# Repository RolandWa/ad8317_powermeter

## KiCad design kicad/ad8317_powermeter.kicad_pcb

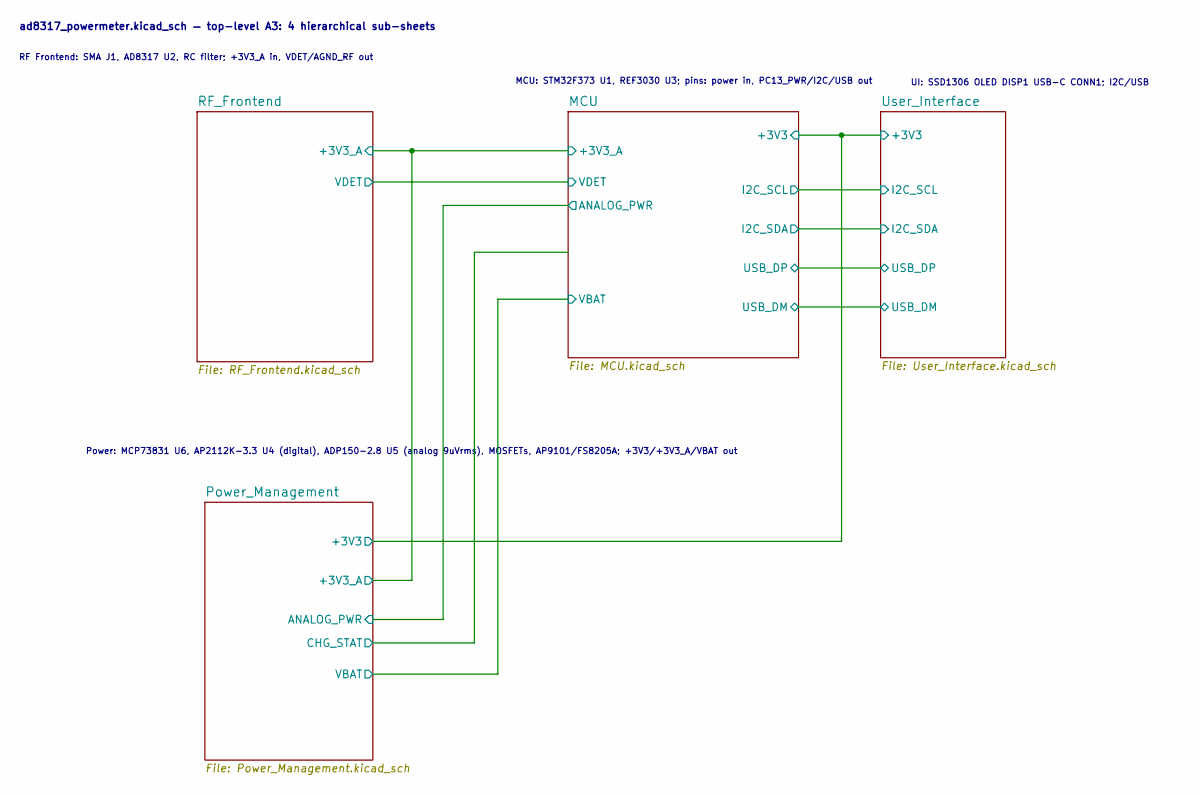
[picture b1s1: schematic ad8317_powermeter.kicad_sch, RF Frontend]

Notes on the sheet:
UI: SSD1306 OLED DISP1 USB-C CONN1; I2C/USB
MCU: STM32F373 U1, REF3030 U3; pins: power in, PC13_PWR/I2C/USB out
RF Frontend: SMA J1, AD8317 U2, RC filter; +3V3_A in, VDET/AGND_RF out
Power: MCP73831 U6, AP2112K-3.3 U4 (digital), ADP150-2.8 U5 (analog 9uVrms), MOSFETs, AP9101/FS8205A; +3V3/+3V3_A/VBAT out
ad8317_powermeter.kicad_sch — top-level A3: 4 hierarchical sub-sheets

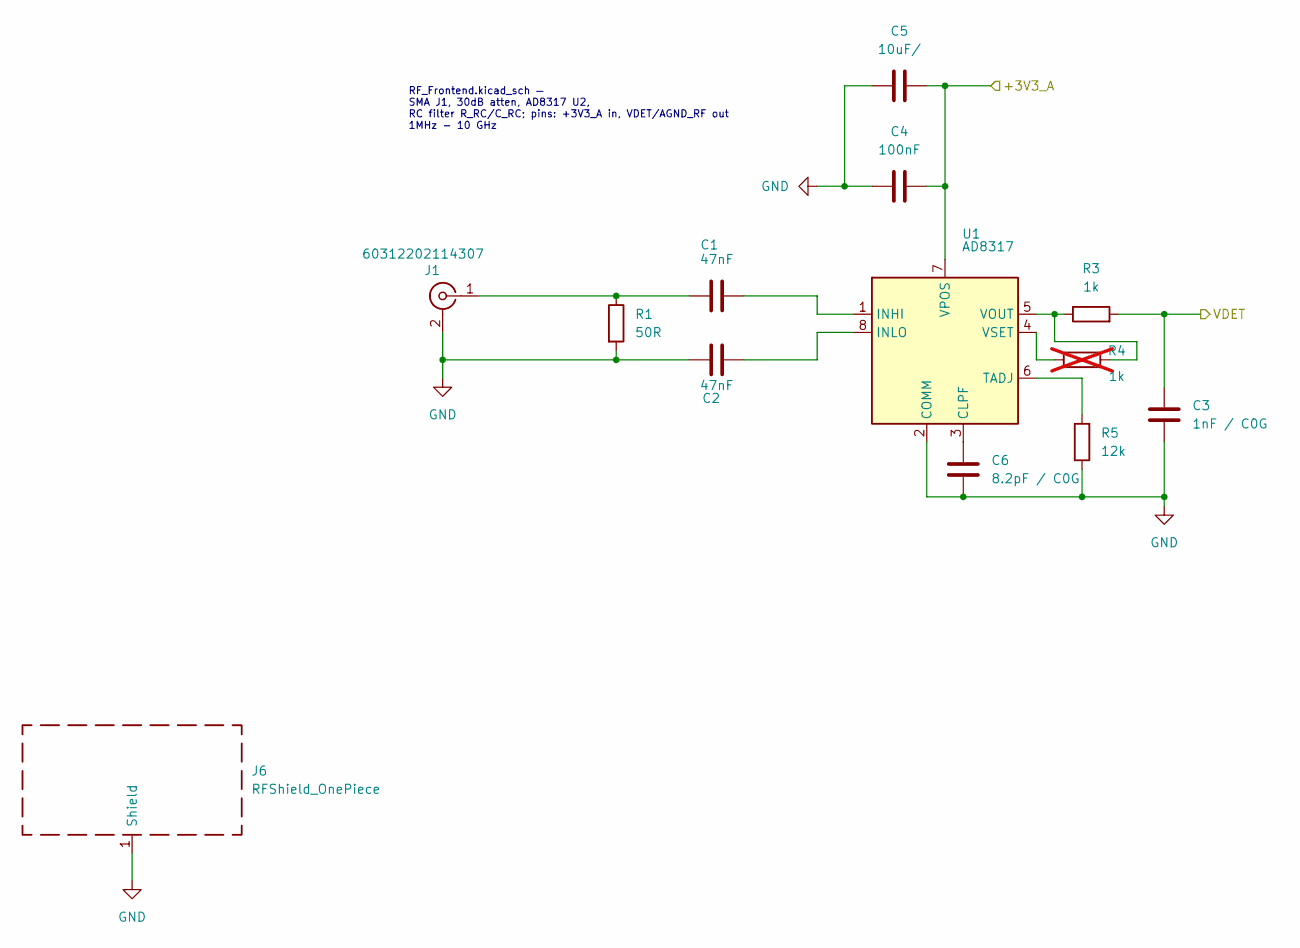
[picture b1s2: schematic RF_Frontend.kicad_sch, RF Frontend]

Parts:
C1, C2: 47nF; C_0402_1005Metric
C3: 1nF / C0G; C_0402_1005Metric
C4: 100nF; C_0402_1005Metric; LCSC C9900014224
C5: 10uF/; C_0805_2012Metric
C6: 8.2pF / C0G; C_0402_1005Metric
J1: 60312202114307; J_Wurth_WR-SMA_60312202114307; Part Number 60312202114307
J6: RFShield_OnePiece; Wuerth_36103305_30x30mm
R1: 50R; R_0402_1005Metric
R3: 1k; R_0402_1005Metric; LCSC C9900199398
R4: 1k; R_0402_1005Metric; not fitted
R5: 12k; R_0402_1005Metric
U1: AD8317; LFCSP-8-1EP_2x3mm_P0.5mm_EP1.6x2.34mm; MPN AD8317ACPZ-REEL7

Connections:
/MCU/+3V3_A: C4.2, C5.2, U1.7 (VPOS); also elsewhere on the board
/MCU/VDET: C3.2, R3.2; also elsewhere on the board
GND: C2.1, C3.1, C4.1, C5.1, C6.1, J1.2 (Ext), J6.1 (Shield_1), R1.2, R5.1, U1.2 (COMM), U1.9; also elsewhere on the board
unnamed: C1.1, J1.1 (In), R1.1
unnamed: C6.2, U1.3 (CLPF)
unnamed: C1.2, U1.1 (INHI)
unnamed: C2.2, U1.8 (INLO)
unnamed: R5.2, U1.6 (TADJ)
unnamed: R3.1, R4.2, U1.5 (VOUT)
unnamed: R4.1, U1.4 (VSET)

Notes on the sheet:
RF_Frontend.kicad_sch — SMA J1, 30dB atten, AD8317 U2, RC filter R_RC/C_RC; pins: +3V3_A in, VDET/AGND_RF out 1MHz - 10 GHz

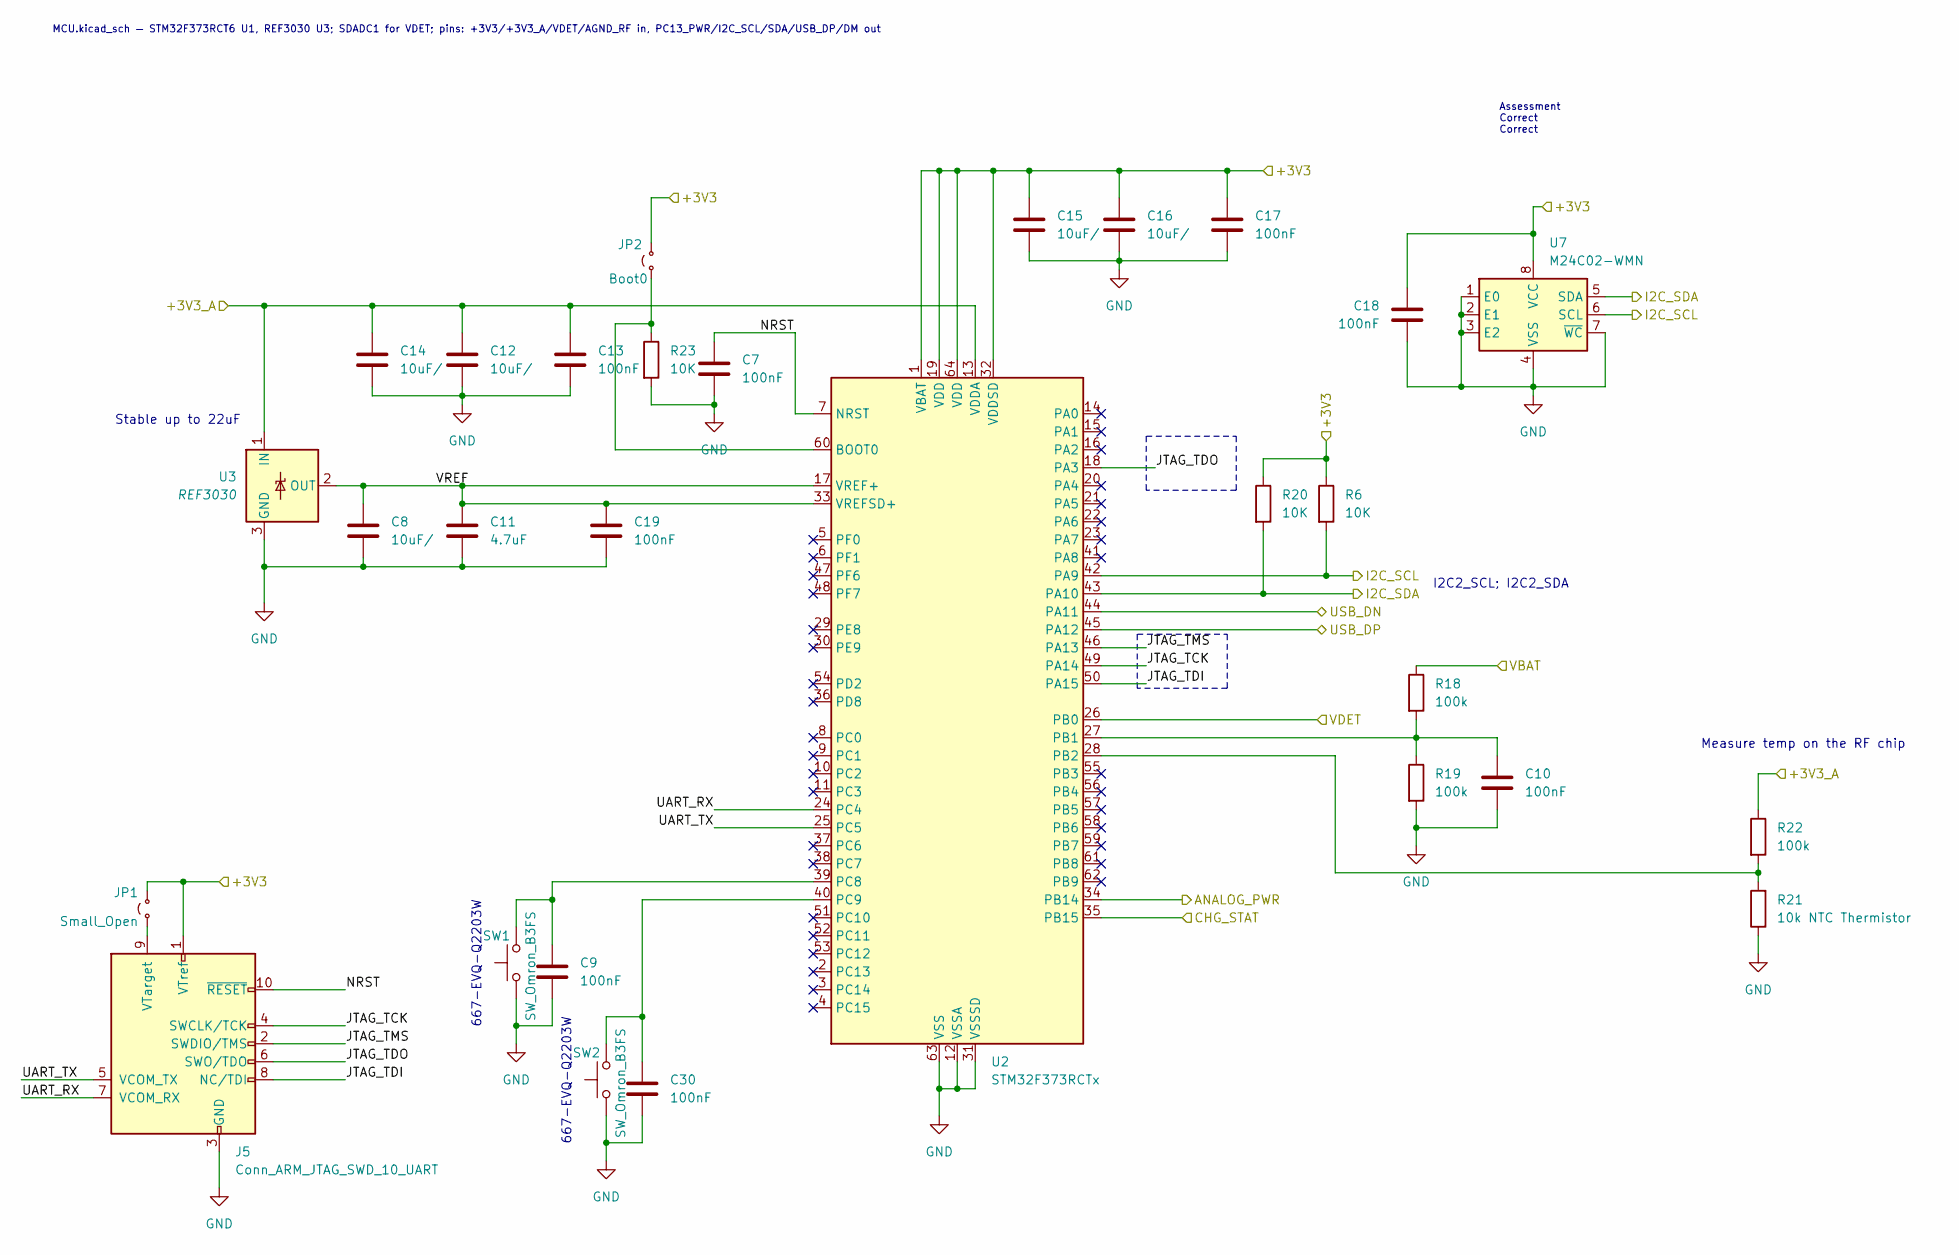
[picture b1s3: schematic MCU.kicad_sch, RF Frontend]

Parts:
C7, C9, C10, C13, C17, C18, C19, C30: 100nF; C_0402_1005Metric; LCSC C9900014224
C8, C12, C14, C15, C16: 10uF/; C_0805_2012Metric
C11: 4.7uF; C_0805_2012Metric
J5: Conn_ARM_JTAG_SWD_10_UART; PinHeader_2x05_P1.27mm_Vertical_SMD
JP1: Small_Open; SolderJumper-2_P1.3mm_Open_RoundedPad1.0x1.5mm
JP2: Boot0; SolderJumper-2_P1.3mm_Open_RoundedPad1.0x1.5mm
R6, R20, R23: 10K; R_0402_1005Metric
R18, R19, R22: 100k; R_0402_1005Metric
R21: 10k NTC Thermistor; C_0402_1005Metric; LCSC C2892547
SW1, SW2: SW_Omron_B3FS; SW_SPST_Omron_B3FS-100xP
U2: STM32F373RCTx; LQFP-64_10x10mm_P0.5mm
U3: REF3030; SOT-23
U7: M24C02-WMN; SOIC-8_3.9x4.9mm_P1.27mm

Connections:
/MCU/+3V3: C15.2, C16.2, C17.2, C18.1, J5.1 (VTref), JP1.2 (B), JP2.2 (B), R6.1, R20.1, U2.1 (VBAT), U2.19 (VDD), U2.32 (VDDSD), U2.64 (VDD), U7.8 (VCC); also elsewhere on the board
/MCU/+3V3_A: C12.2, C13.2, C14.2, R22.1, U2.13 (VDDA), U3.1 (IN); also elsewhere on the board
/MCU/ANALOG_PWR: U2.34 (PB14); also elsewhere on the board
/MCU/CHG_STAT: U2.35 (PB15); also elsewhere on the board
/MCU/I2C_SCL: R6.2, U2.42 (PA9), U7.6 (SCL); also elsewhere on the board
/MCU/I2C_SDA: R20.2, U2.43 (PA10), U7.5 (SDA); also elsewhere on the board
/MCU/JTAG_TCK: J5.4 (SWCLK/TCK), U2.49 (PA14)
/MCU/JTAG_TDI: J5.8 (NC/TDI), U2.50 (PA15)
/MCU/JTAG_TDO: J5.6 (SWO/TDO), U2.18 (PA3)
/MCU/JTAG_TMS: J5.2 (SWDIO/TMS), U2.46 (PA13)
/MCU/NRST: C7.2, J5.10 (~RESET), U2.7 (NRST)
/MCU/UART_RX: J5.7 (VCOM_RX), U2.24 (PC4)
/MCU/UART_TX: J5.5 (VCOM_TX), U2.25 (PC5)
/MCU/USB_DN: U2.44 (PA11); also elsewhere on the board
/MCU/USB_DP: U2.45 (PA12); also elsewhere on the board
/MCU/VBAT: R18.1; also elsewhere on the board
/MCU/VDET: U2.26 (PB0); also elsewhere on the board
/MCU/VREF: C8.2, C11.2, C19.2, U2.17 (VREF+), U2.33 (VREFSD+), U3.2 (OUT)
GND: C7.1, C8.1, C9.1, C10.1, C11.1, C12.1, C13.1, C14.1, C15.1, C16.1, C17.1, C18.2, C19.1, C30.1, J5.3 (GND), R19.2, R21.1, R23.2, SW1.1, SW2.1, U2.12 (VSSA), U2.31 (VSSSD), U2.63 (VSS), U3.3 (GND), U7.1 (E0), U7.2 (E1), U7.3 (E2), U7.4 (VSS), U7.7 (~WC); also elsewhere on the board
unnamed: J5.9 (VTarget), JP1.1 (A)
unnamed: JP2.1 (A), R23.1, U2.60 (BOOT0)
unnamed: C10.2, R18.2, R19.1, U2.27 (PB1)
unnamed: R21.2, R22.2, U2.28 (PB2)
unnamed: C9.2, SW1.2, U2.39 (PC8)
unnamed: C30.2, SW2.2, U2.40 (PC9)

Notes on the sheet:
Assessment Correct Correct
667-EVQ-Q2203W
Stable up to 22uF
Measure temp on the RF chip
MCU.kicad_sch — STM32F373RCT6 U1, REF3030 U3; SDADC1 for VDET; pins: +3V3/+3V3_A/VDET/AGND_RF in, PC13_PWR/I2C_SCL/SDA/USB_DP/DM out
I2C2_SCL; I2C2_SDA

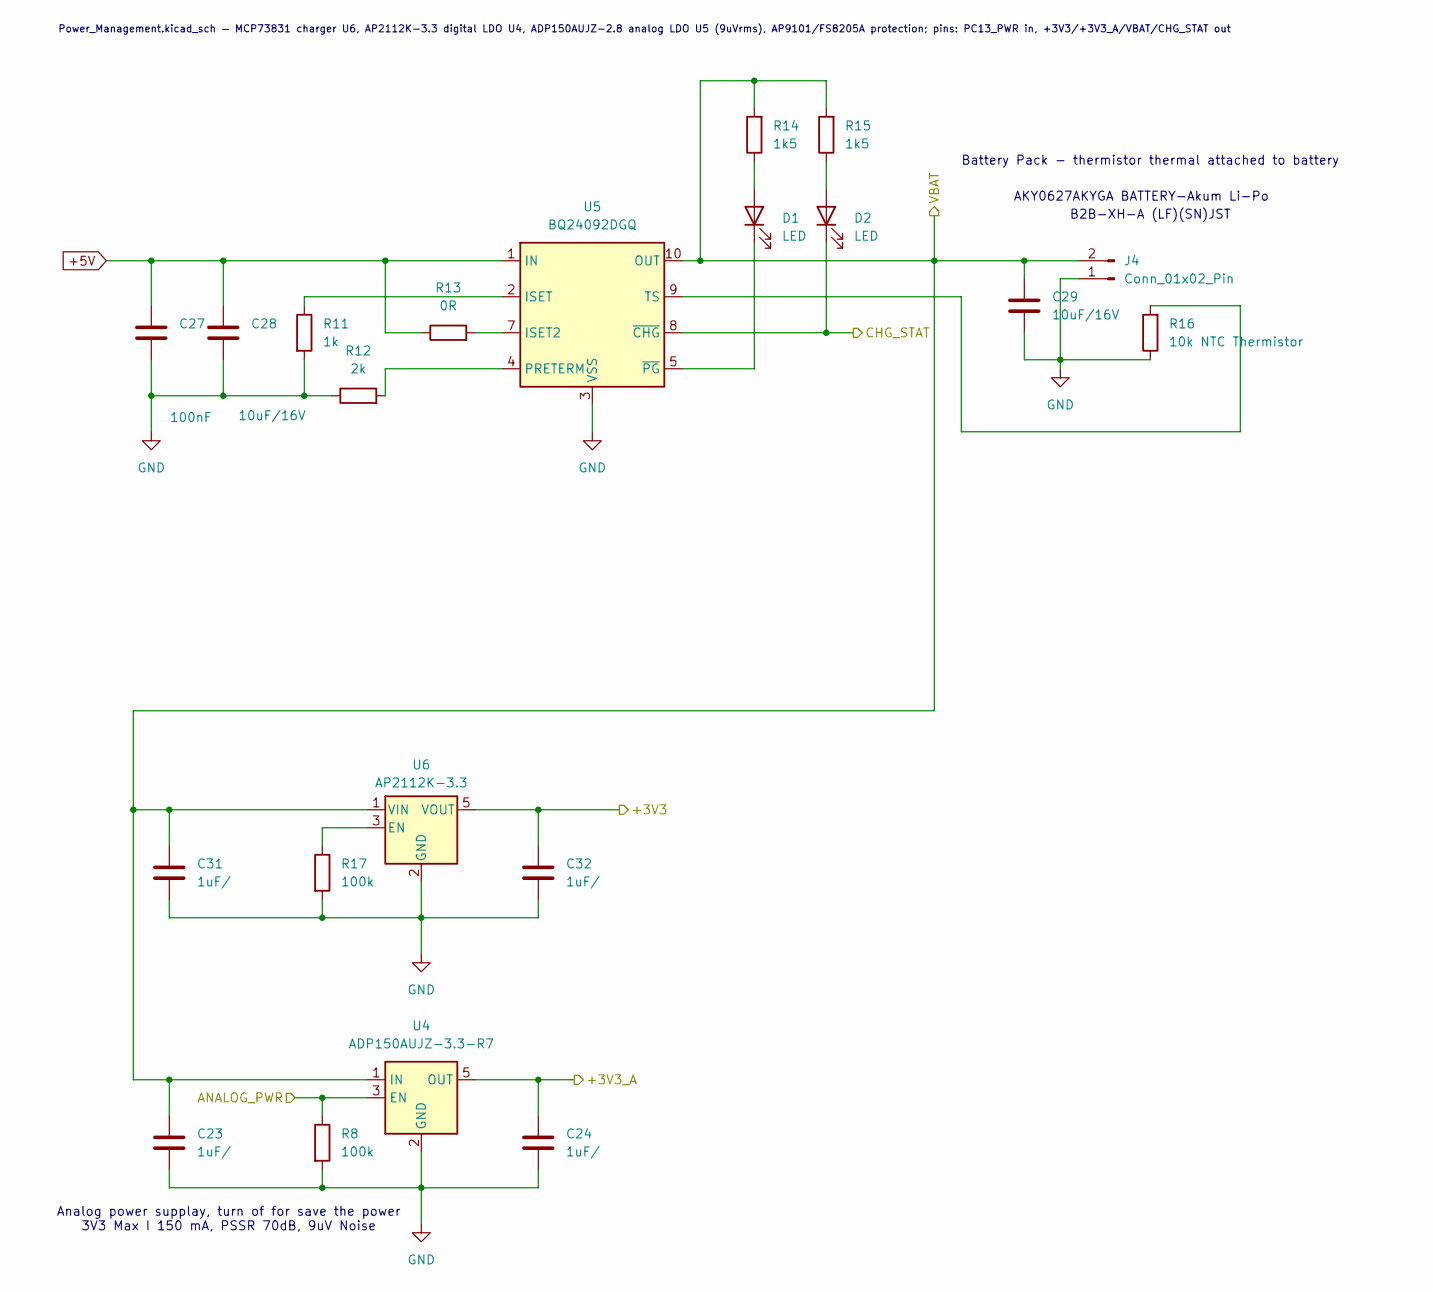
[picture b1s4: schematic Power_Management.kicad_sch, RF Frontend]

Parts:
C23, C24, C31, C32: 1uF/; C_0402_1005Metric
C27: 100nF; C_0402_1005Metric; LCSC C9900014224
C28, C29: 10uF/16V; C_0805_2012Metric; LCSC C9900019493
D1, D2: LED; LED_0402_1005Metric; LCSC C9900022508
J4: Conn_01x02_Pin; JST_XH_B2B-XH-AM_1x02_P2.50mm_Vertical; LCSC C161869
R8, R17: 100k; R_0402_1005Metric
R11: 1k; R_0402_1005Metric; LCSC C9900199398
R12: 2k; R_0402_1005Metric; LCSC C140225
R13: 0R; R_0402_1005Metric; LCSC C140225
R14, R15: 1k5; R_0402_1005Metric; LCSC C269672
R16: 10k NTC Thermistor; C_0402_1005Metric; LCSC C2892547
U4: ADP150AUJZ-3.3-R7; TSOT-23-5
U5: BQ24092DGQ; HVSSOP-10-1EP_3x3mm_P0.5mm_EP1.83x1.89mm_ThermalVias; Digikey BQ24092DGQT
U6: AP2112K-3.3; SOT-23-5

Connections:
+5V: C27.1, C28.1, R13.1, U5.1 (IN); also elsewhere on the board
/MCU/+3V3: C32.2, U6.5 (VOUT); also elsewhere on the board
/MCU/+3V3_A: C24.2, U4.5 (OUT); also elsewhere on the board
/MCU/ANALOG_PWR: R8.1, U4.3 (EN); also elsewhere on the board
/MCU/CHG_STAT: D2.1 (K), U5.8 (~CHG); also elsewhere on the board
/MCU/VBAT: C23.2, C29.1, C31.2, J4.2, R14.2, R15.2, U4.1 (IN), U5.10 (OUT), U6.1 (VIN); also elsewhere on the board
GND: C23.1, C24.1, C27.2, C28.2, C29.2, C31.1, C32.1, J4.1, R8.2, R11.2, R12.1, R16.1, R17.2, U4.2 (GND), U5.3 (VSS), U5.11 (VSS), U6.2 (GND); also elsewhere on the board
unnamed: D1.2 (A), R14.1
unnamed: D1.1 (K), U5.5 (~PG)
unnamed: D2.2 (A), R15.1
unnamed: R13.2, U5.7 (ISET2)
unnamed: R11.1, U5.2 (ISET)
unnamed: R12.2, U5.4 (PRETERM)
unnamed: R16.2, U5.9 (TS)
unnamed: R17.1, U6.3 (EN)

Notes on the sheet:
Battery Pack - thermistor thermal attached to battery
B2B-XH-A (LF)(SN)JST
Power_Management.kicad_sch — MCP73831 charger U6, AP2112K-3.3 digital LDO U4, ADP150AUJZ-2.8 analog LDO U5 (9uVrms), AP9101/FS8205A protection; pins: PC13_PWR in, +3V3/+3V3_A/VBAT/CHG_STAT out
AKY0627AKYGA BATTERY-Akum Li-Po
Analog power supplay, turn of for save the power 3V3 Max I 150 mA, PSSR 70dB, 9uV Noise

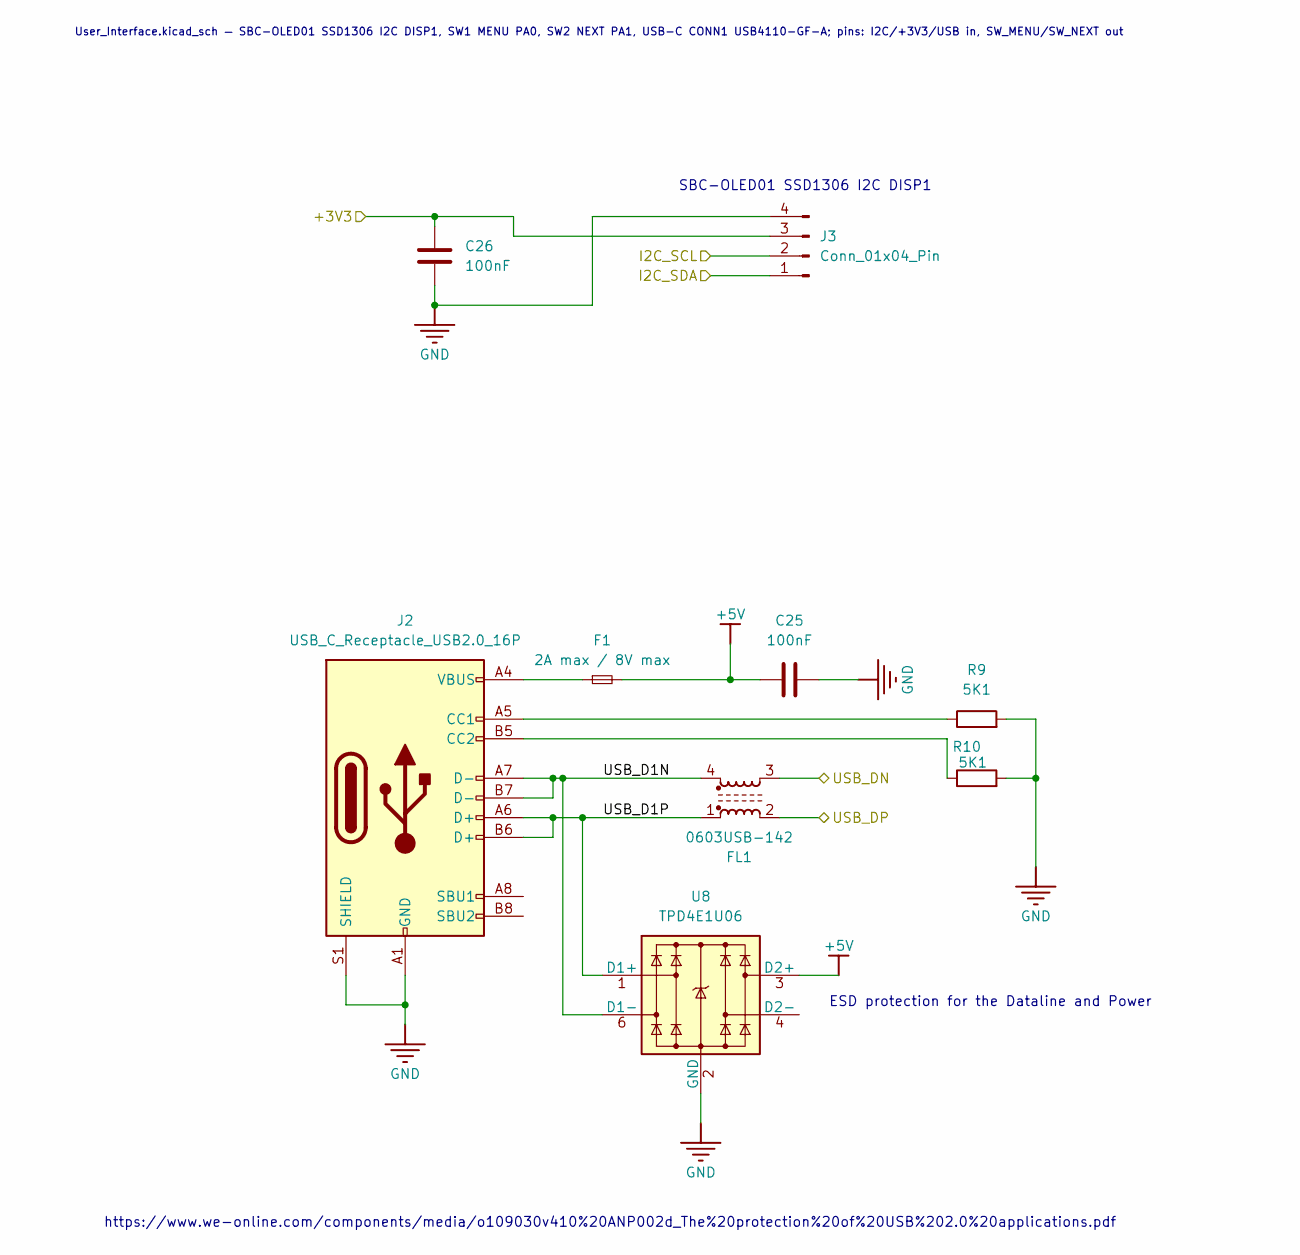
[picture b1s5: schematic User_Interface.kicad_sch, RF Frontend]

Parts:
C25, C26: 100nF; C_0402_1005Metric; LCSC C9900014224
F1: 2A max / 8V max; Fuse_1812_4532Metric_Pad1.30x3.40mm_HandSolder
FL1: 0603USB-142; L_CommonModeChoke_Coilcraft_0603USB
J2: USB_C_Receptacle_USB2.0_16P; USB_C_Receptacle_G-Switch_GT-USB-7010ASV
J3: Conn_01x04_Pin; PinHeader_1x04_P2.54mm_Vertical
R9, R10: 5K1; R_0402_1005Metric_Pad0.72x0.64mm_HandSolder; LCSC C5913162
U8: TPD4E1U06; SOT-23-6

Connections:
+5V: C25.2, F1.2, U8.3 (D2+); also elsewhere on the board
/MCU/+3V3: C26.2, J3.3; also elsewhere on the board
/MCU/I2C_SCL: J3.2; also elsewhere on the board
/MCU/I2C_SDA: J3.1; also elsewhere on the board
/MCU/USB_DN: FL1.3; also elsewhere on the board
/MCU/USB_DP: FL1.2; also elsewhere on the board
/User_Interface/USB_D1N: FL1.4, J2.A7 (D-), J2.B7 (D-), U8.6 (D1-)
/User_Interface/USB_D1P: FL1.1, J2.A6 (D+), J2.B6 (D+), U8.1 (D1+)
GND: C25.1, C26.1, J2.A1 (GND), J2.A12 (GND), J2.B1 (GND), J2.B12 (GND), J2.S1 (SHIELD), J3.4, R9.2, R10.2, U8.2 (GND); also elsewhere on the board
unnamed: F1.1, J2.A4 (VBUS), J2.A9 (VBUS), J2.B4 (VBUS), J2.B9 (VBUS)
unnamed: J2.A5 (CC1), R9.1
unnamed: J2.B5 (CC2), R10.1

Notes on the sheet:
ESD protection for the Dataline and Power
SBC-OLED01 SSD1306 I2C DISP1
https://www.we-online.com/components/media/o109030v410%20ANP002d_The%20protection%20of%20USB%202.0%20applications.pdf
User_Interface.kicad_sch — SBC-OLED01 SSD1306 I2C DISP1, SW1 MENU PA0, SW2 NEXT PA1, USB-C CONN1 USB4110-GF-A; pins: I2C/+3V3/USB in, SW_MENU/SW_NEXT out

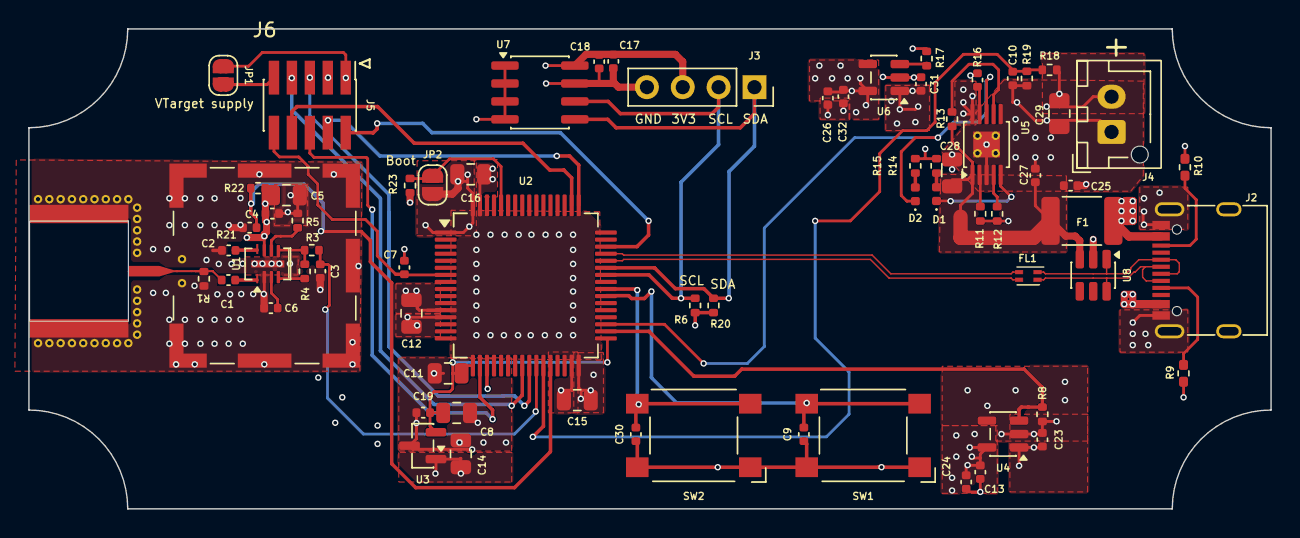
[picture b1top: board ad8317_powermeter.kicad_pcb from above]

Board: 4 copper layers, 88.0 x 34.0 mm, 72 parts (0 on the bottom side), 46 nets.

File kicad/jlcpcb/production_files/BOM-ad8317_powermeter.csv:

Comment,Designator,Footprint,LCSC,Quantity
0R,R13,R_0402_1005Metric,C140225,1
100R,"R1,R2",R_0402_1005Metric,C25076,2
100k,"R17,R18,R19,R22,R8",R_0402_1005Metric,C25530,5
100nF,"C10,C13,C17,C18,C19,C25,C26,C27,C30,C4,C7,C9",C_0402_1005Metric,C9900014224,12
10K,"R20,R23,R6",R_0402_1005Metric,C25531,3
10k NTC Thermistor,"R16,R21",C_0402_1005Metric,C2892547,2
10uF/,"C12,C14,C15,C16,C5,C8",C_0805_2012Metric,C1713,6
10uF/16V,"C28,C29",C_0805_2012Metric,C77075,2
12k,R5,R_0402_1005Metric,C25752,1
1k,"R11,R3",R_0402_1005Metric,C9900199398,2
1k5,"R14,R15",R_0402_1005Metric,C269672,2
1nF / C0G,C3,C_0402_1005Metric,C76947,1
1uF/,"C23,C24,C31,C32",C_0402_1005Metric,C2887021,4
2k,R12,R_0402_1005Metric,C140225,1
4.7uF,C11,C_0805_2012Metric,C1779,1
47nF,"C1,C2",C_0402_1005Metric,C880605,2
5K1,"R10,R9",R_0402_1005Metric_Pad0.72x0.64mm_HandSolder,C5913162,2
8.2pF / C0G,C6,C_0402_1005Metric,C1579,1
AD8317,U1,LFCSP-8-1EP_2x3mm_P0.5mm_EP1.6x2.34mm,C578693,1
ADP150AUJZ-3.3-R7,U4,TSOT-23-5,C42432300,1
AP2112K-3.3,U6,SOT-23-5,C51118,1
BQ24092DGQ,U5,HVSSOP-10-1EP_3x3mm_P0.5mm_EP1.83x1.89mm_ThermalVias,C2864890,1
Conn_01x02_Pin,J4,JST_XH_B2B-XH-AM_1x02_P2.50mm_Vertical,C161869,1
LED,"D1,D2",LED_0402_1005Metric,C9900022508,2
M24C02-WMN,U7,SOIC-8_3.9x4.9mm_P1.27mm,C7562,1
REF3030,U3,SOT-23,C38423,1
TPD4E1U06,U8,SOT-23-6,C124691,1
USB_C_Receptacle_USB2.0_16P,J2,USB_C_Receptacle_G-Switch_GT-USB-7010ASV,,1
Small_Open,JP1,SolderJumper-2_P1.3mm_Open_RoundedPad1.0x1.5mm,,1
0603USB-142,FL1,L_CommonModeChoke_Coilcraft_0603USB,,1
Conn_ARM_JTAG_SWD_10_UART,J5,PinHeader_2x05_P1.27mm_Vertical_SMD,,1
SW_Omron_B3FS,SW1,SW_SPST_Omron_B3FS-100xP,,1
STM32F373RCTx,U2,LQFP-64_10x10mm_P0.5mm,,1
Boot0,JP2,SolderJumper-2_P1.3mm_Open_RoundedPad1.0x1.5mm,,1
SW_Omron_B3FS,SW2,SW_SPST_Omron_B3FS-100xP,,1
2A max / 8V max,F1,Fuse_1812_4532Metric_Pad1.30x3.40mm_HandSolder,,1
RFShield_OnePiece,J6,Laird_Technologies_BMI-S-101_13.66x12.70mm_custom,,1
